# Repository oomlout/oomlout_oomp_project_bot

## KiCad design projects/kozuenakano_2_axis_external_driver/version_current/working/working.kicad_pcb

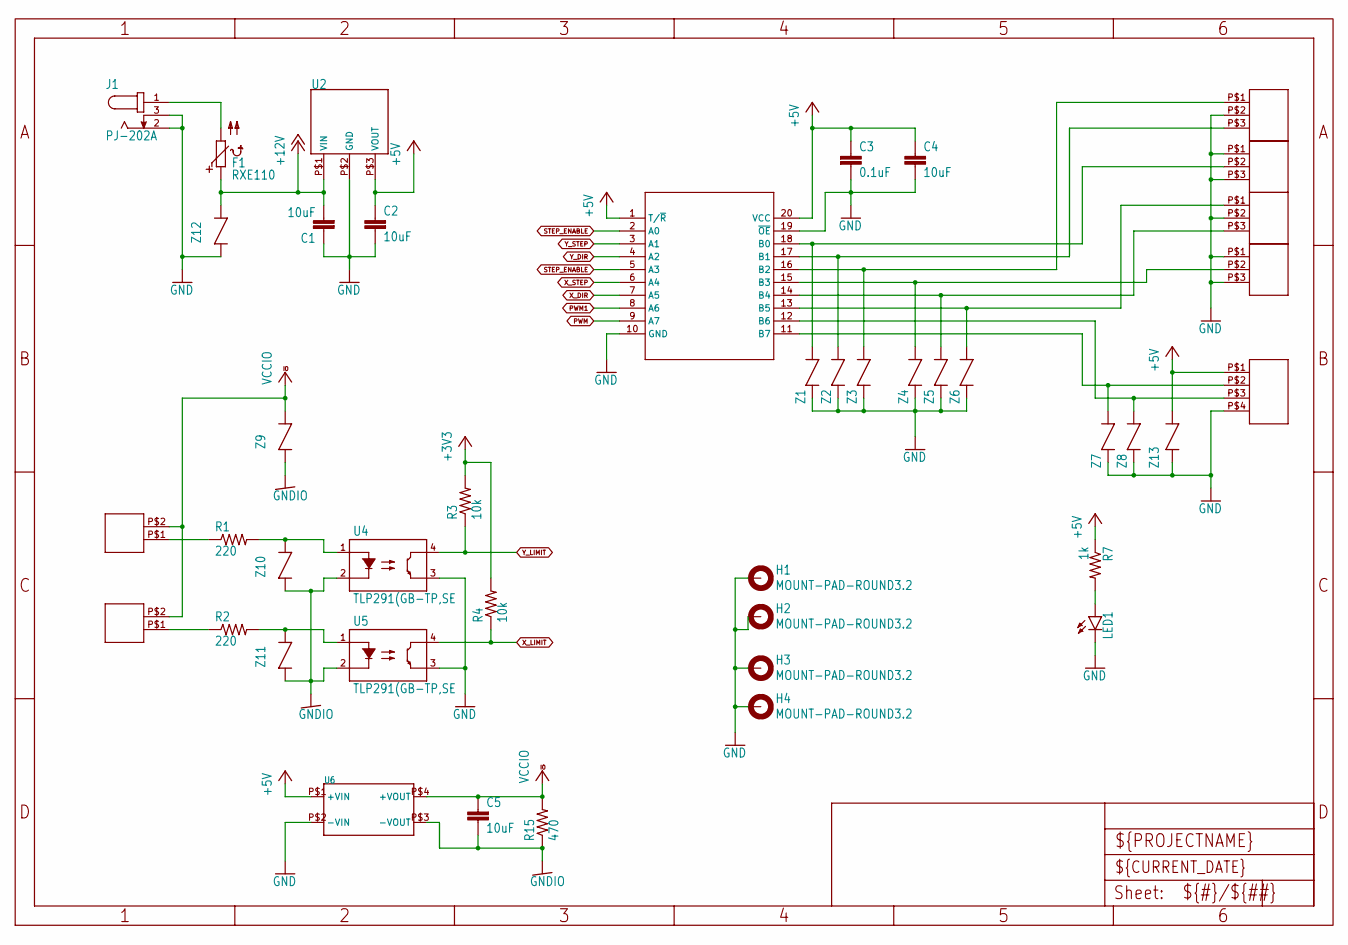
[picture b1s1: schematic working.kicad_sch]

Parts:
C1, C2, C4, C5: 10uF; C0805
C3: 0.1uF; C0603
CN1, CN2, CN3, CN4: ETB43034G000Z
CN7: ETB43044G000Z
CN8, CN9: ETB43024G000Z
F1: RXE110
H1, H2, H3, H4: MOUNT-PAD-ROUND3.2; 3,2-PAD
J1: PJ-202A; CUI_PJ-202A
LED1: LED3MM
R1, R2: 220; R0603
R3, R4: 10k; R0603
R7: 1k; R0603
R15: 470; R0603
U2: BP5293-50BP5293_SIDE; BP5293_SIDE
U3: MC74ACT245DWR2G; SOIC-20WB_ONS
U4, U5: TLP291(GB-TP,SE; SOIC127P700X220-4N
U6: MAU102; MAU100_SINGLE
Z1, Z2, Z3, Z4, Z5, Z6, Z7, Z8, Z9, Z10, Z11, Z13: MLVC06V012C210; 0603
Z12: MLVC06V026C120; 0603

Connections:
+3V3: R3.2, R4.2; also elsewhere on the board
+5V: C2.2, C3.1, C4.2, CN7.P$1 (1), R7.1, U2.P$3 (VOUT), U3.1 (T/~R), U3.20 (VCC), U6.P$1 (+VIN), Z13.1; also elsewhere on the board
+12V: C1.2, F1.P$1 (1), U2.P$1 (VIN), Z12.1
GND: C1.1, C2.1, C3.2, C4.1, CN1.P$1 (1), CN1.P$3 (3), CN2.P$2 (2), CN3.P$1 (1), CN3.P$3 (3), CN4.P$2 (2), CN7.P$4 (4), H1.B3,2, H2.B3,2, H3.B3,2, H4.B3,2, J1.2, J1.3, LED1.K (C), U2.P$2 (GND), U3.10 (GND), U3.19 (~OE), U4.3 (EMIT), U5.3 (EMIT), U6.P$2 (-VIN), Z1.2, Z2.2, Z3.2, Z4.2, Z5.2, Z6.2, Z7.2, Z8.2, Z12.2, Z13.2; also elsewhere on the board
GNDIO: C5.1, R15.1, U4.2 (C), U5.2 (C), U6.P$3 (-VOUT), Z9.2, Z10.2, Z11.2
LED1_PWM_5: CN7.P$3 (3), U3.12 (B6), Z8.1
LED_PWM_5: CN7.P$2 (2), U3.11 (B7), Z7.1
unnamed: F1.P$2 (2), J1.1
unnamed: LED1.A, R7.2
unnamed: R1.2, U4.1 (A), Z10.1
unnamed: R2.2, U5.1 (A), Z11.1
PWM: U3.9 (A7); also elsewhere on the board
PWM1: U3.8 (A6); also elsewhere on the board
STEP_ENABLE: U3.2 (A0), U3.5 (A3); also elsewhere on the board
STEP_EN_X_5: CN3.P$2 (2), U3.15 (B3), Z4.1
STEP_EN_Y_5: CN1.P$2 (2), U3.18 (B0), Z1.1
VCCIO: C5.2, CN8.P$2 (2), CN9.P$2 (2), R15.2, U6.P$4 (+VOUT), Z9.1
X_DIR: U3.7 (A5); also elsewhere on the board
X_DIR_5: CN4.P$1 (1), U3.13 (B5), Z6.1
X_LIMIT: R4.1, U5.4 (COL); also elsewhere on the board
X_LIMIT_IO: CN9.P$1 (1), R2.1
X_STEP: U3.6 (A4); also elsewhere on the board
X_STEP_5: CN4.P$3 (3), U3.14 (B4), Z5.1
Y_DIR: U3.4 (A2); also elsewhere on the board
Y_DIR_5: CN2.P$1 (1), U3.16 (B2), Z3.1
Y_LIMIT: R3.1, U4.4 (COL); also elsewhere on the board
Y_LIMIT_IO: CN8.P$1 (1), R1.1
Y_STEP: U3.3 (A1); also elsewhere on the board
Y_STEP_5: CN2.P$3 (3), U3.17 (B1), Z2.1

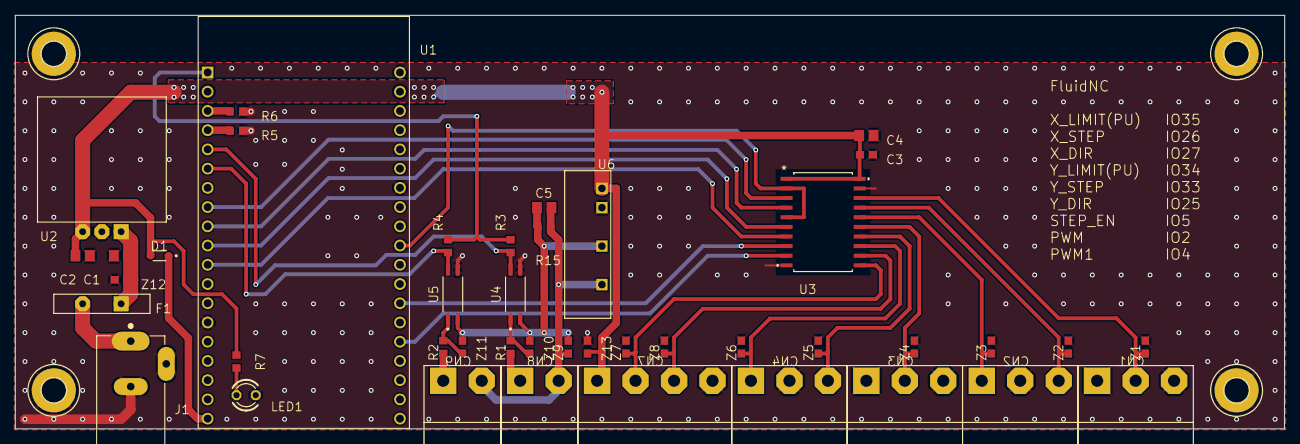
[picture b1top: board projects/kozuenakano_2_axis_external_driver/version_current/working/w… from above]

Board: 2 copper layers, 167.6 x 54.6 mm, 47 parts (0 on the bottom side), 32 nets.

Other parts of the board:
D1: BAT760-7; SOD2513X120N
R5, R6: 100k; R0603
U1: ESP32-DEVKITC-32D; MODULE_ESP32-DEVKITC-32D

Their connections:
+3V3: U1.1; also elsewhere on the board
+5V: D1.A; also elsewhere on the board
GND: R5.1, R6.1, U1.14, U1.20, U1.26; also elsewhere on the board
unnamed: D1.C, U1.19
unnamed: R6.2, U1.3
unnamed: R5.2, U1.4
PWM: U1.34; also elsewhere on the board
PWM1: U1.32; also elsewhere on the board
STEP_ENABLE: U1.29; also elsewhere on the board
X_DIR: U1.11; also elsewhere on the board
X_LIMIT: U1.6; also elsewhere on the board
X_STEP: U1.10; also elsewhere on the board
Y_DIR: U1.9; also elsewhere on the board
Y_LIMIT: U1.5; also elsewhere on the board
Y_STEP: U1.8; also elsewhere on the board

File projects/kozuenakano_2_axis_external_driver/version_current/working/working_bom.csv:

"Id";"Designator";"Footprint";"Quantity";"Designation";"Supplier and ref";
1;"C5,C2,C1,C4";"C0805";4;"10uF";;;
2;"Z13,Z9,Z7,Z3,Z1,Z11,Z4,Z6,Z5,Z8,Z10,Z2";"0603";12;"MLVC06V012C210";;;
3;"CN1,CN4,CN3,CN2";"ETB43034G000Z";4;"ETB43034G000Z";;;
4;"LED1";"LED3MM";1;"";;;
5;"R6,R5";"R0603";2;"100k";;;
6;"U5,U4";"SOIC127P700X220-4N";2;"TLP291(GB-TP,SE";;;
7;"C3";"C0603";1;"0.1uF";;;
8;"R7";"R0603";1;"1k";;;
9;"H2,H4,H3,H1";"3,2-PAD";4;"MOUNT-PAD-ROUND3.2";;;
10;"R3,R4";"R0603";2;"10k";;;
11;"Z12";"0603";1;"MLVC06V026C120";;;
12;"J1";"CUI_PJ-202A";1;"PJ-202A";;;
13;"CN8,CN9";"ETB43024G000Z";2;"ETB43024G000Z";;;
14;"U3";"SOIC-20WB_ONS";1;"MC74ACT245DWR2G";;;
15;"D1";"SOD2513X120N";1;"BAT760-7";;;
16;"CN7";"ETB43044G000Z";1;"ETB43044G000Z";;;
17;"U6";"MAU100_SINGLE";1;"MAU102";;;
18;"F1";"RXE110";1;"RXE110";;;
19;"U1";"MODULE_ESP32-DEVKITC-32D";1;"ESP32-DEVKITC-32D";;;
20;"R1,R2";"R0603";2;"220";;;
21;"R15";"R0603";1;"470";;;
22;"U2";"BP5293_SIDE";1;"BP5293-50BP5293_SIDE";;;

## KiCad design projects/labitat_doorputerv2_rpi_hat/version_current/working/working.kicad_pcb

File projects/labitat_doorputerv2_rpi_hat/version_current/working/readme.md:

# doorputerv2_rpi_hat by labitat  
This is a harvested standardized copy of a project from github.  
The original project can be found at:  
https://github.com/labitat/doorputerv2_rpi_hat  
Please consult that link for additional, details, files, and license information.  
Note: It was auto harvested and if the original repo had more than one board file or anything out of the ordinary the files here are likely not representative.

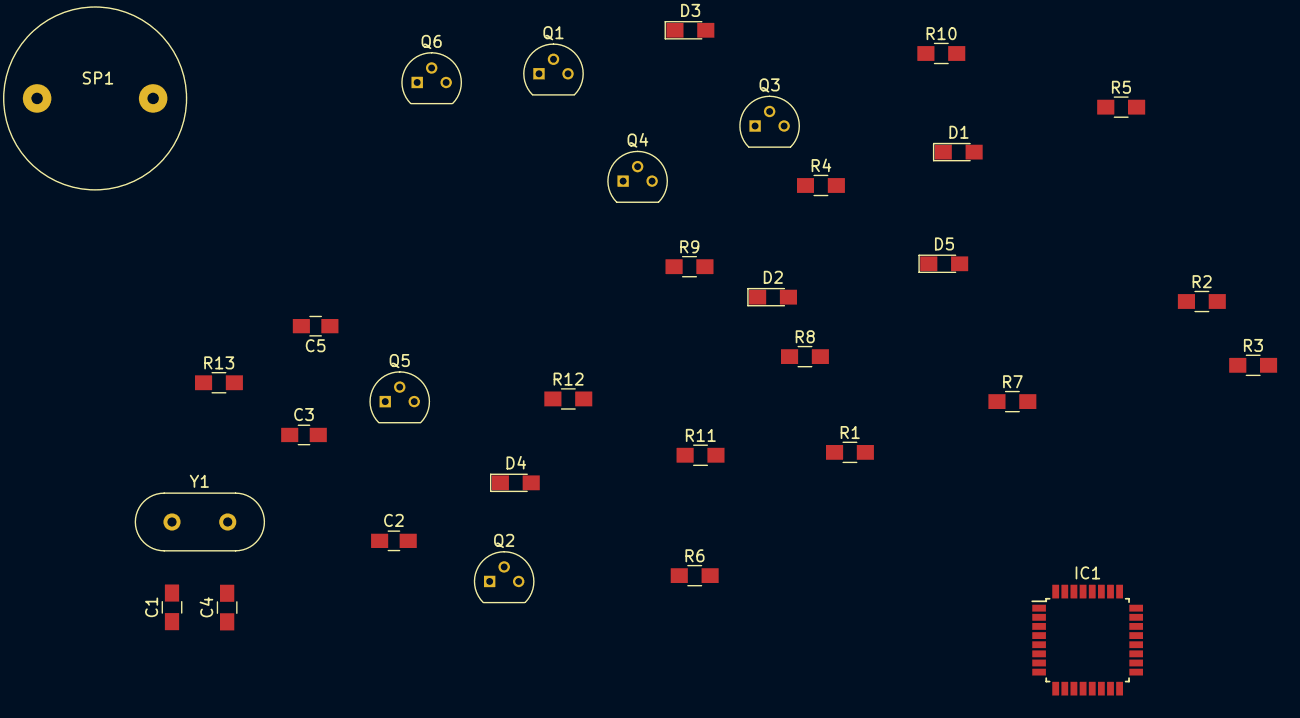
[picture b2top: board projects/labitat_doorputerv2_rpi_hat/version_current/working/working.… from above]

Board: 2 copper layers, 32 parts (0 on the bottom side), 23 nets, no tracks yet.

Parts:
C1, C4: 22pF; C_0805_HandSoldering
C2, C3, C5: 100nF; C_0805_HandSoldering
D1, D2, D3, D4, D5: LED; LED_0805_HandSoldering
IC1: ATMEGA328P; LQFP-32_7x7mm_Pitch0.8mm
Q1, Q2, Q3, Q4, Q5, Q6: BC547; TO-92_Molded_Narrow
R1, R2, R3, R4, R5, R6, R7, R8, R9, R10, R11, R12: R_Small; R_0805_HandSoldering
R13: 10K; R_0805_HandSoldering
SP1: BUZZER
Y1: 16MHz; Crystal_HC49-U_Vertical

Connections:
+5V: C2.2, C3.2, IC1.4, IC1.6, IC1.18, IC1.20, R1.1, R2.1, R3.1, R4.1, R5.1, R11.1, R13.1
/Arduino/avr_reset: C5.2, IC1.29, R13.2
GND: C1.1, C2.1, C3.1, C4.1, C5.1, IC1.3, IC1.5, IC1.21, Q1.3, Q2.3, Q3.3, Q4.3, Q5.3, Q6.3
unnamed: C1.2, IC1.7, Y1.1
unnamed: C4.2, IC1.8, Y1.2
unnamed: D1.1, Q1.1
unnamed: D1.2, R1.2
unnamed: D2.1, Q2.1
unnamed: D2.2, R2.2
unnamed: D3.1, Q3.1
unnamed: D3.2, R3.2
unnamed: D4.1, Q4.1
unnamed: D4.2, R4.2
unnamed: D5.1, Q5.1
unnamed: D5.2, R5.2
unnamed: Q1.2, R6.2
unnamed: Q2.2, R7.2
unnamed: Q3.2, R8.2
unnamed: Q4.2, R9.2
unnamed: Q5.2, R10.2
unnamed: Q6.1, SP1.2
unnamed: Q6.2, R12.2
unnamed: R11.2, SP1.1

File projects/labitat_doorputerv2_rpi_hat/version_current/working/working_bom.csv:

"Id";"Designator";"Footprint";"Quantity";"Designation";"Supplier and ref";
1;"C1,C4";"C_0805_HandSoldering";2;"22pF";;;
2;"C2,C3,C5";"C_0805_HandSoldering";3;"100nF";;;
3;"D1,D2,D3,D4,D5";"LED_0805_HandSoldering";5;"LED";;;
4;"IC1";"LQFP-32_7x7mm_Pitch0.8mm";1;"ATMEGA328P";;;
5;"Q1,Q2,Q3,Q4,Q5,Q6";"TO-92_Molded_Narrow";6;"BC547";;;
6;"R1,R2,R3,R4,R5,R6,R7,R8,R9,R10,R11,R12";"R_0805_HandSoldering";12;"R_Small";;;
7;"R13";"R_0805_HandSoldering";1;"10K";;;
8;"SP1";"BUZZER";1;"BUZZER";;;
9;"Y1";"Crystal_HC49-U_Vertical";1;"16MHz";;;

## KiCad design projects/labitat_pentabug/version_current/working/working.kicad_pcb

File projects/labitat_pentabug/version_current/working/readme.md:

# pentabug by labitat  
This is a harvested standardized copy of a project from github.  
The original project can be found at:  
https://github.com/labitat/pentabug  
Please consult that link for additional, details, files, and license information.  
Note: It was auto harvested and if the original repo had more than one board file or anything out of the ordinary the files here are likely not representative.

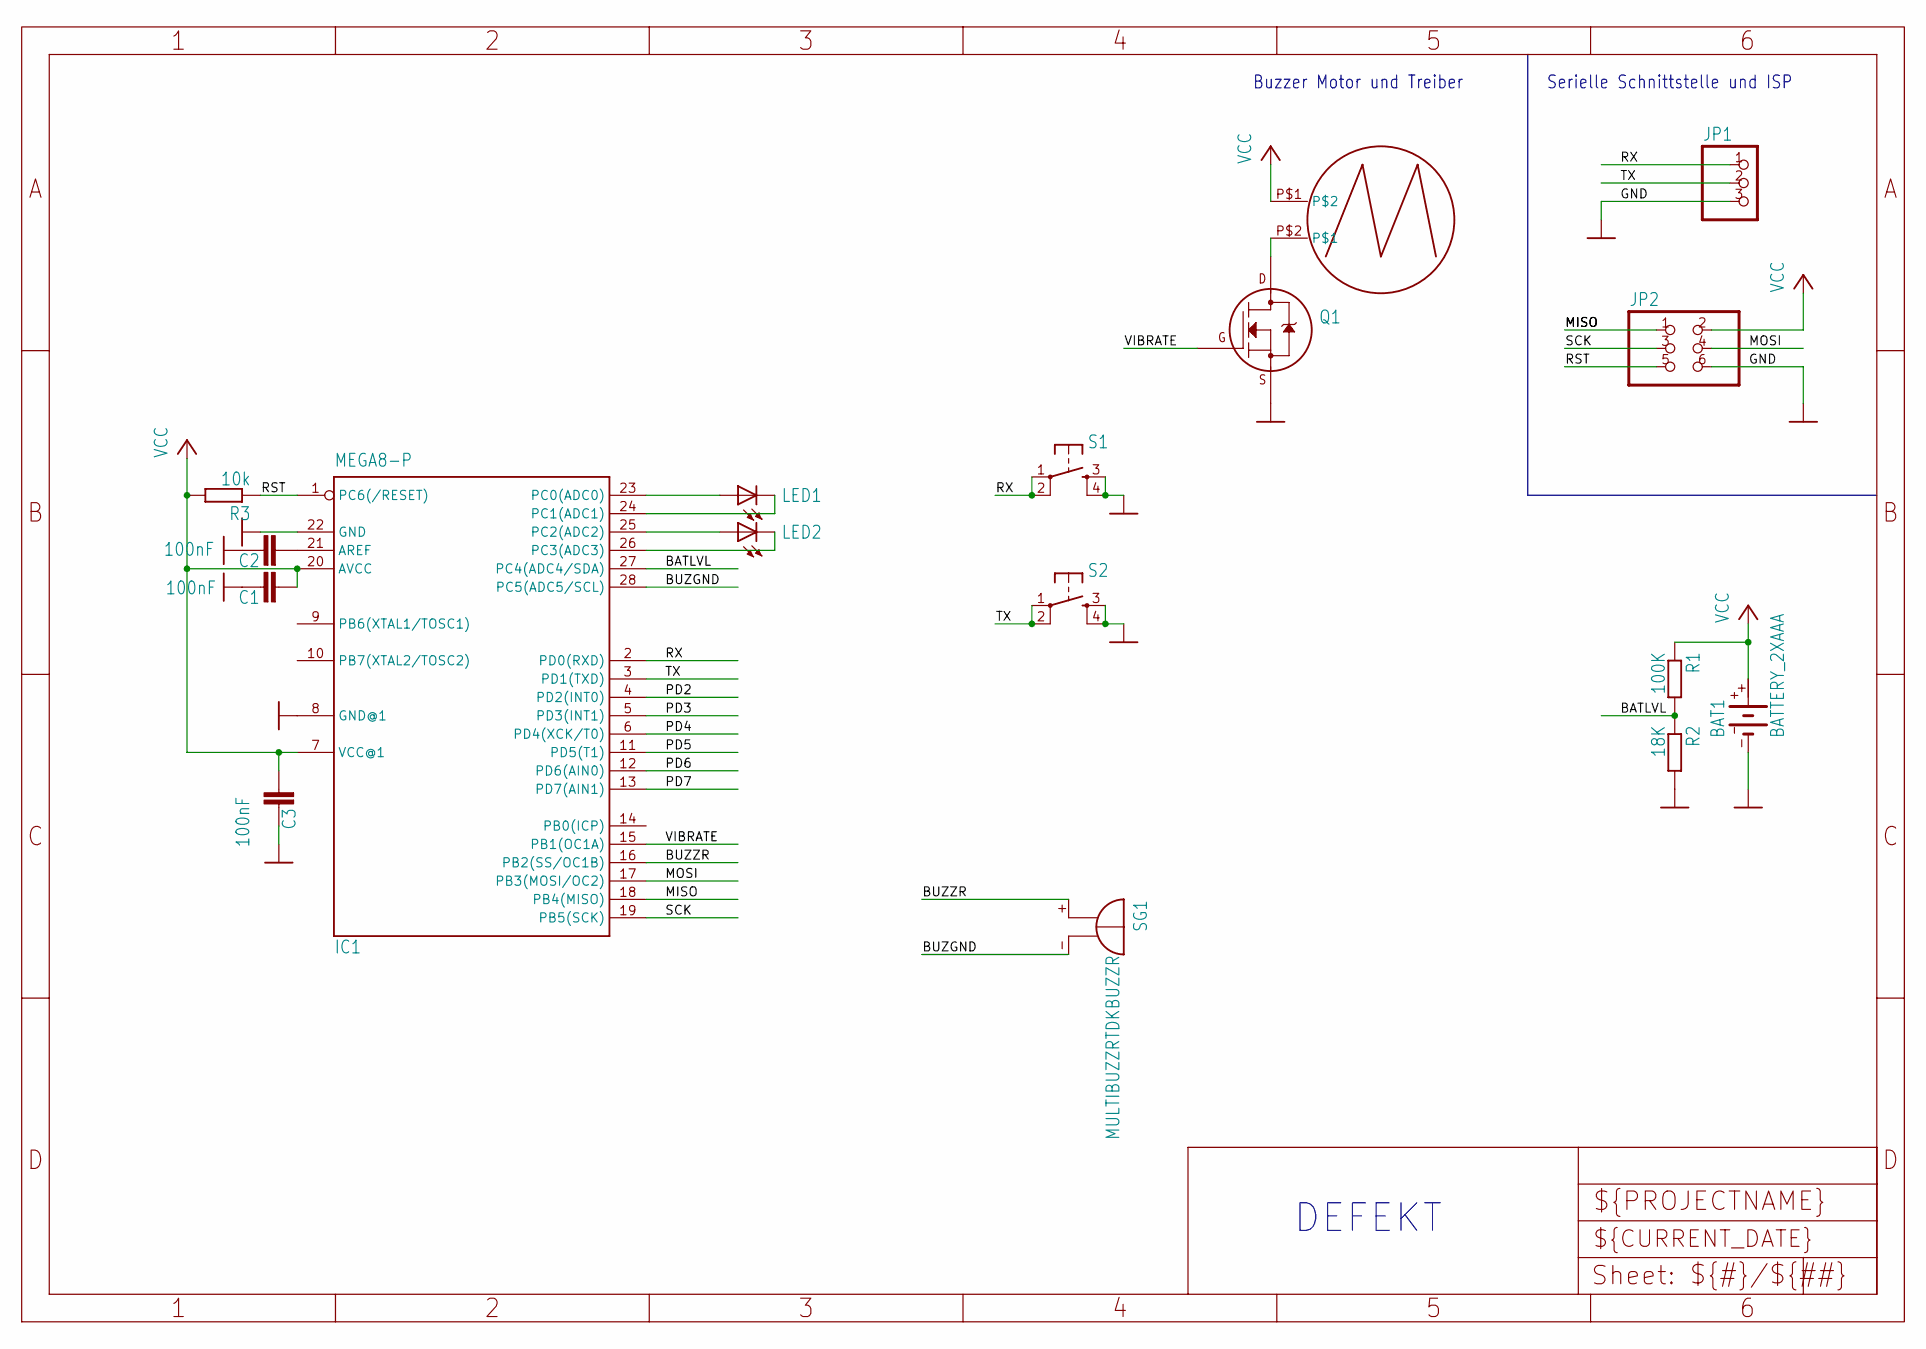
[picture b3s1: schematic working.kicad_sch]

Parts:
BAT1: BATTERY_2XAAA
C1, C2, C3: 100nF; C025-024X044
IC1: MEGA8-P; DIL28-3
JP1: PINHD-1X3; 1X03
JP2: PINHD-2X3; 2X03
LED1, LED2: LED5MM
Q1: 2N700_TO92; TO-92
R1: 100K; 0207_10
R2: 18K; 0207_10
R3: 10k; 0207_10
S1, S2: TAC_SWITCHPTH; TACTILE-PTH
SG1: MULTIBUZZRTDKBUZZR; BUZZRTDK
U$1: VIBRAMOTOR; LA4-432

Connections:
BATLVL: IC1.27 (PC4(ADC4/SDA)), R1.2, R2.1
BATTLVL: IC1.26 (PC3(ADC3)), LED2.K (C)
BUZGND: IC1.28 (PC5(ADC5/SCL)), SG1.-
BUZZR: IC1.16 (PB2(SS/OC1B)), SG1.+
GND: BAT1.-, C1.1, C2.1, C3.1, IC1.8 (GND@1), IC1.22 (GND), JP1.3, JP2.6, Q1.1 (S), R2.2, S1.3, S1.4, S2.3, S2.4
MISO: IC1.18 (PB4(MISO)), JP2.1
MOSI: IC1.17 (PB3(MOSI/OC2)), JP2.4
unnamed: IC1.23 (PC0(ADC0)), LED1.A
unnamed: IC1.25 (PC2(ADC2)), LED2.A
unnamed: Q1.3 (D), U$1.P$2
unnamed: IC1.24 (PC1(ADC1)), LED1.K (C)
unnamed: C2.2, IC1.21 (AREF)
PD2: IC1.4 (PD2(INT0))
PD3: IC1.5 (PD3(INT1))
PD4: IC1.6 (PD4(XCK/T0))
PD5: IC1.11 (PD5(T1))
PD6: IC1.12 (PD6(AIN0))
PD7: IC1.13 (PD7(AIN1))
RST: IC1.1 (PC6(/RESET)), JP2.5, R3.1
RX: IC1.2 (PD0(RXD)), JP1.1, S1.1, S1.2
SCK: IC1.19 (PB5(SCK)), JP2.3
TX: IC1.3 (PD1(TXD)), JP1.2, S2.1, S2.2
VCC: BAT1.+, C1.2, C3.2, IC1.7 (VCC@1), IC1.20 (AVCC), JP2.2, R1.1, R3.2, U$1.P$1
VIBRATE: IC1.15 (PB1(OC1A)), Q1.2 (G)

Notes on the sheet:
Buzzer Motor und Treiber
DEFEKT~{}
Serielle Schnittstelle und ISP

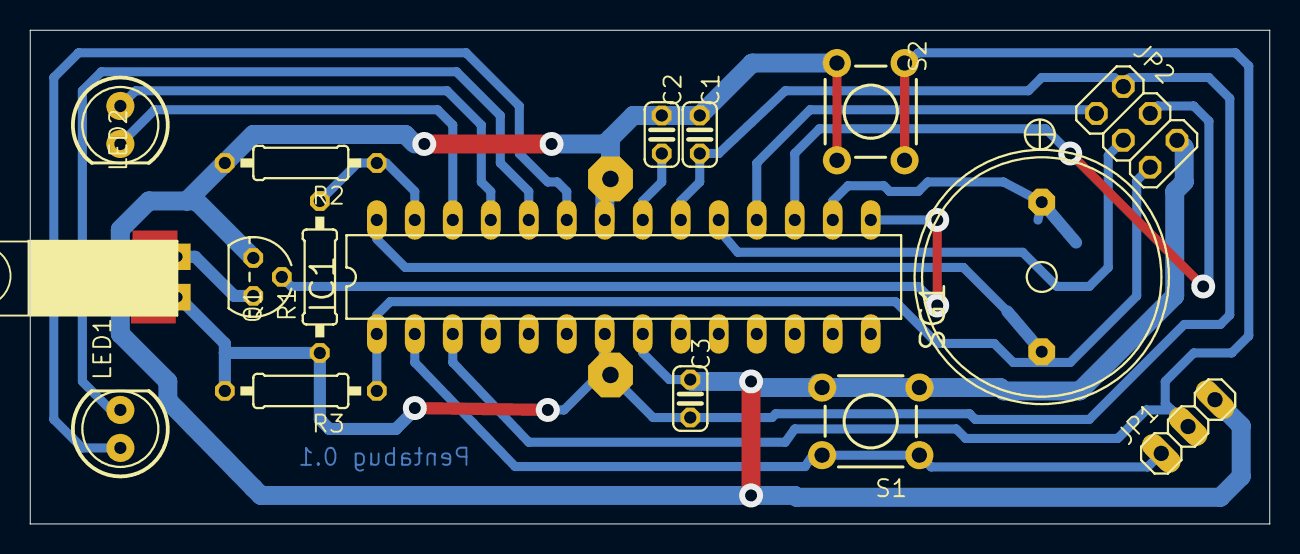
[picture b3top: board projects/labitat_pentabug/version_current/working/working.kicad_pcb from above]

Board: 2 copper layers, 82.9 x 33.0 mm, 17 parts (1 on the bottom side), 18 nets.

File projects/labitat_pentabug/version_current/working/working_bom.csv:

"Id";"Designator";"Footprint";"Quantity";"Designation";"Supplier and ref";
1;"JP1";"1X03";1;"";;;
2;"C3,C2,C1";"C025-024X044";3;"100nF";;;
3;"R2";"0207_10";1;"18K";;;
4;"IC1";"DIL28-3";1;"ATMEGA88";;;
5;"R3";"0207_10";1;"10k";;;
6;"SG1";"BUZZRTDK";1;"MULTIBUZZRTDKBUZZR";;;
7;"U$1";"LA4-432";1;"VIBRAMOTOR";;;
8;"S1,S2";"TACTILE-PTH";2;"";;;
9;"R1";"0207_10";1;"100K";;;
10;"LED2,LED1";"LED5MM";2;"";;;
11;"Q1";"TO-92";1;"";;;
12;"JP2";"2X03";1;"";;;
13;"BAT1";"BATTERY_2XAAA";1;"BATTERY_2XAAA";;;

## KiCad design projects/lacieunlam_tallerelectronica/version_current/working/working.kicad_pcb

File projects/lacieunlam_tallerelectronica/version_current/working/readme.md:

# TallerElectronica by LacieUnlam  
This is a harvested standardized copy of a project from github.  
The original project can be found at:  
https://github.com/LacieUnlam/TallerElectronica  
Please consult that link for additional, details, files, and license information.  
Note: It was auto harvested and if the original repo had more than one board file or anything out of the ordinary the files here are likely not representative.

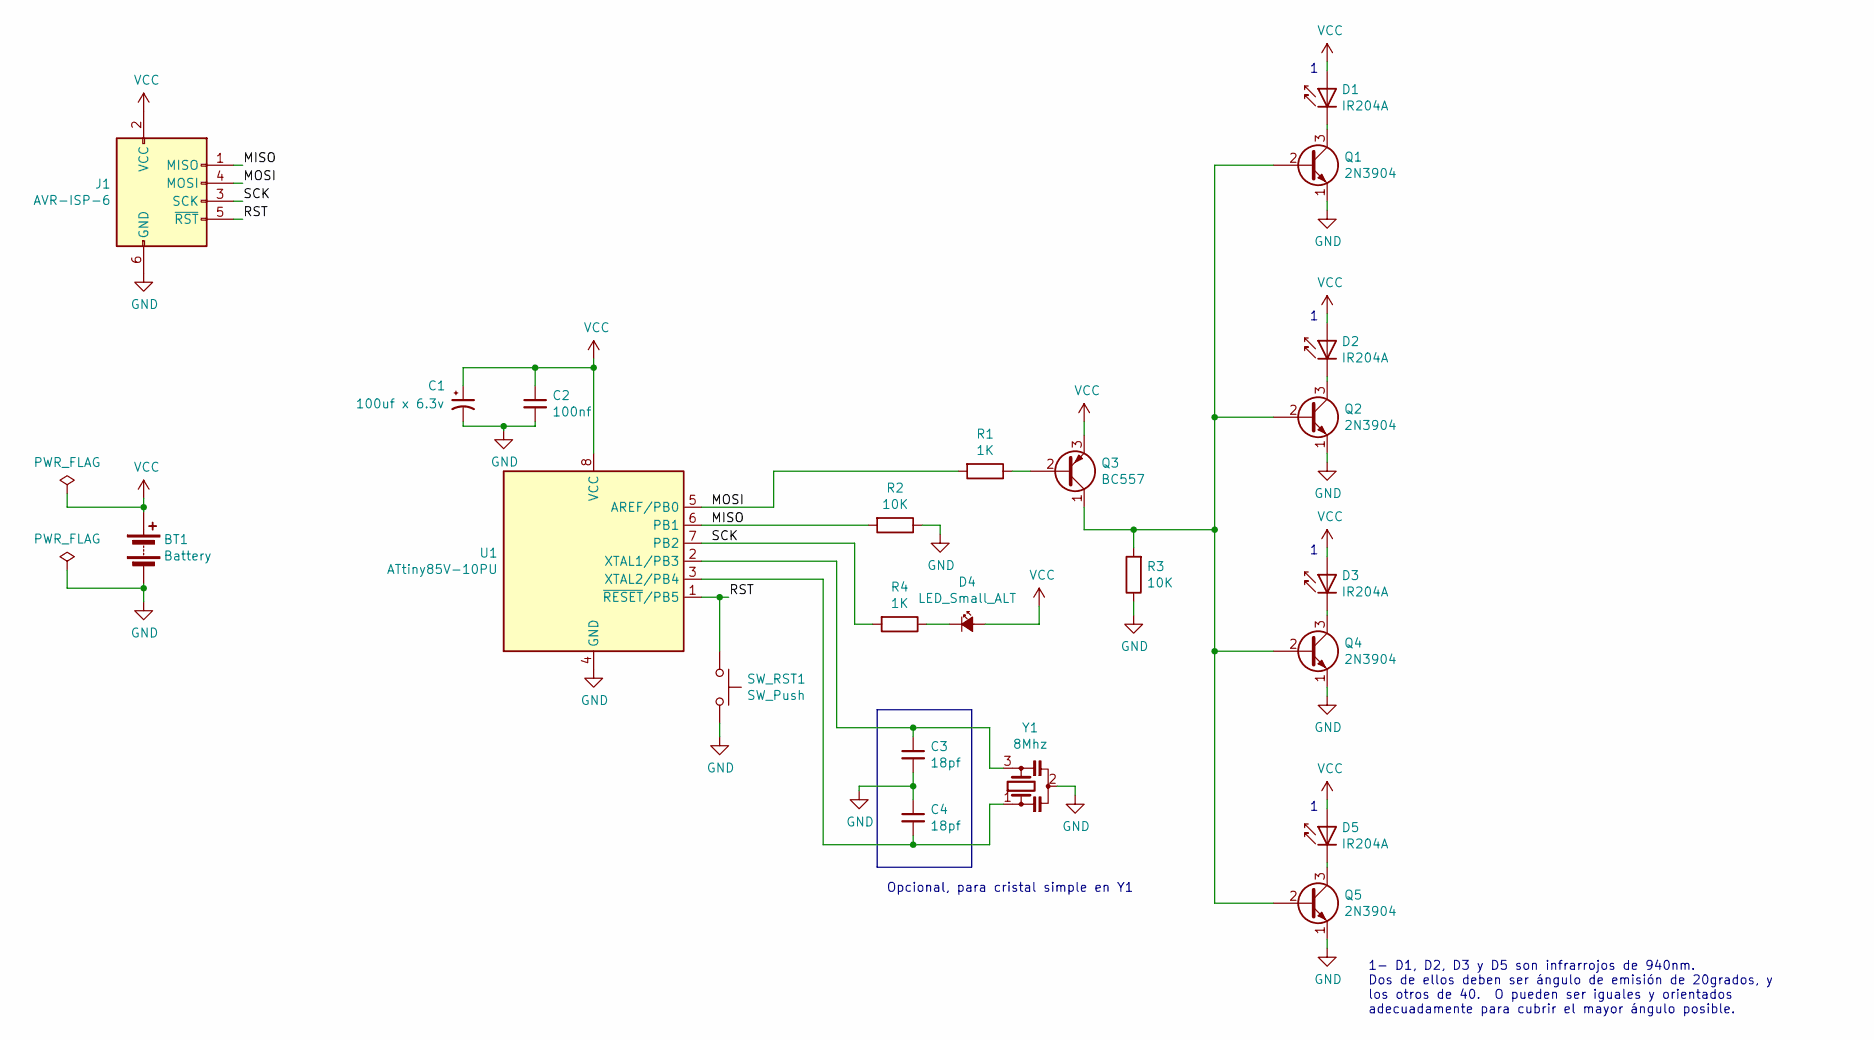
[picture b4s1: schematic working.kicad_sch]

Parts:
BT1: Battery; PinHeader_1x02_P2.54mm_Vertical
C1: 100uf x 6.3v; CP_Radial_D6.3mm_P2.50mm
C2: 100nf; C_Disc_D7.5mm_W2.5mm_P5.00mm
C3, C4: 18pf; C_Disc_D3.0mm_W2.0mm_P2.50mm
D1, D2, D3, D5: IR204A; LED_D3.0mm_IRBlack
D4: LED_Small_ALT; LED_D3.0mm
J1: AVR-ISP-6; PinHeader_2x03_P2.54mm_Vertical
Q1, Q2, Q4, Q5: 2N3904; TO-92_Inline
Q3: BC557; TO-92_Inline
R1, R4: 1K; R_Axial_DIN0309_L9.0mm_D3.2mm_P12.70mm_Horizontal
R2, R3: 10K; R_Axial_DIN0309_L9.0mm_D3.2mm_P12.70mm_Horizontal
SW_RST1: SW_Push; SW_PUSH_6mm_H5mm
U1: ATtiny85V-10PU; DIP-8_W7.62mm
Y1: 8Mhz; Resonator-3Pin_W10.0mm_H5.0mm

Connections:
/MISO: J1.1 (MISO), R2.2, U1.6 (PB1)
/MOSI: J1.4 (MOSI), R1.2, U1.5 (AREF/PB0)
/RST: J1.5 (~RST), SW_RST1.1, U1.1 (~RESET/PB5)
/SCK: J1.3 (SCK), R4.2, U1.7 (PB2)
GND: BT1.2 (-), C1.2, C2.2, C3.2, C4.1, J1.6 (GND), Q1.1 (E), Q2.1 (E), Q4.1 (E), Q5.1 (E), R2.1, R3.1, SW_RST1.2, U1.4 (GND), Y1.2
unnamed: C3.1, U1.2 (XTAL1/PB3), Y1.3
unnamed: C4.2, U1.3 (XTAL2/PB4), Y1.1
unnamed: D1.1 (K), Q1.3 (C)
unnamed: D2.1 (K), Q2.3 (C)
unnamed: D3.1 (K), Q4.3 (C)
unnamed: D4.1 (K), R4.1
unnamed: D5.1 (K), Q5.3 (C)
unnamed: Q1.2 (B), Q2.2 (B), Q3.1 (C), Q4.2 (B), Q5.2 (B), R3.2
unnamed: Q3.2 (B), R1.1
VCC: BT1.1 (+), C1.1, C2.1, D1.2 (A), D2.2 (A), D3.2 (A), D4.2 (A), D5.2 (A), J1.2 (VCC), Q3.3 (E), U1.8 (VCC)

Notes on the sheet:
Opcional, para cristal simple en Y1
1- D1, D2, D3 y D5 son infrarrojos de 940nm. Dos de ellos deben ser ángulo de emisión de 20grados, y los otros de 40. O pueden ser iguales y orientados adecuadamente para cubrir el mayor ángulo posible.

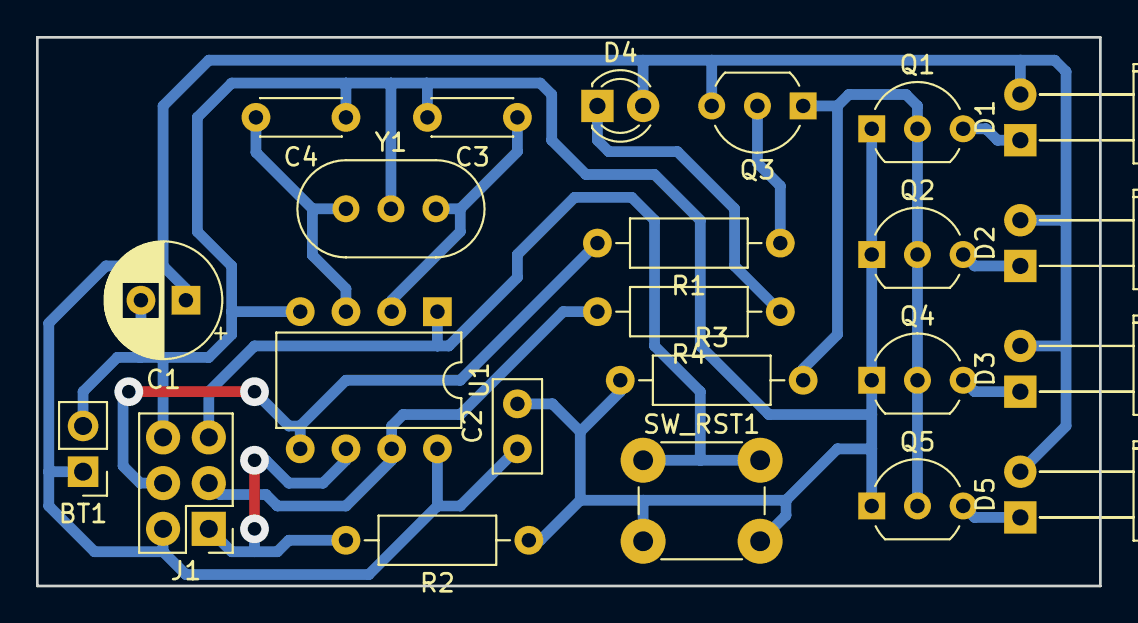
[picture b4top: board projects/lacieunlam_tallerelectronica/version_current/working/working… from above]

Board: 2 copper layers, 59.1 x 30.5 mm, 23 parts (0 on the bottom side), 15 nets.

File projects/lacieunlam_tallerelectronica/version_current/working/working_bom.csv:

"Id";"Designator";"Footprint";"Quantity";"Designation";"Supplier and ref";
1;"R1,R4";"R_Axial_DIN0207_L6.3mm_D2.5mm_P10.16mm_Horizontal";2;"1K";;;
2;"R2,R3";"R_Axial_DIN0207_L6.3mm_D2.5mm_P10.16mm_Horizontal";2;"10K";;;
3;"SW_RST1";"SW_PUSH_6mm_H5mm";1;"SW_Push";;;
4;"J1";"PinHeader_2x03_P2.54mm_Vertical";1;"AVR-ISP-6";;;
5;"C1";"CP_Radial_D6.3mm_P2.50mm";1;"100uf x 6.3v";;;
6;"C4,C3";"C_Disc_D4.3mm_W1.9mm_P5.00mm";2;"18pf";;;
7;"C2";"C_Disc_D5.0mm_W2.5mm_P2.50mm";1;"100nf";;;
8;"Q3";"TO-92_Inline_Wide";1;"BC557";;;
9;"Q1,Q2,Q4,Q5";"TO-92_Inline_Wide";4;"2N3904";;;
10;"D2,D3,D5,D1";"LED_D5.0mm_Horizontal_O6.35mm_Z3.0mm";4;"IR204A";;;
11;"BT1";"PinHeader_1x02_P2.54mm_Vertical";1;"Battery";;;
12;"D4";"LED_D3.0mm";1;"LED_Small_ALT";;;
13;"U1";"DIP-8_W7.62mm";1;"ATtiny85V-10PU";;;
14;"Y1";"Resonator-3Pin_W10.0mm_H5.0mm";1;"8Mhz";;;

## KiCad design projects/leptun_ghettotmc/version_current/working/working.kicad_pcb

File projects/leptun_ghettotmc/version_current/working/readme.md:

# OOMP Project  
## GhettoTMC  by leptun  
  
oomp key: oomp_projects_flat_leptun_ghettotmc  
(snippet of original readme)  
  
GhettoTMC  
  
  full source readme at [readme_src.md](readme_src.md)  
  
source repo at: [https://github.com/leptun/GhettoTMC](https://github.com/leptun/GhettoTMC)  
## Board  

## Schematic  

[schematic pdf](working_schematic.pdf)  
## Images

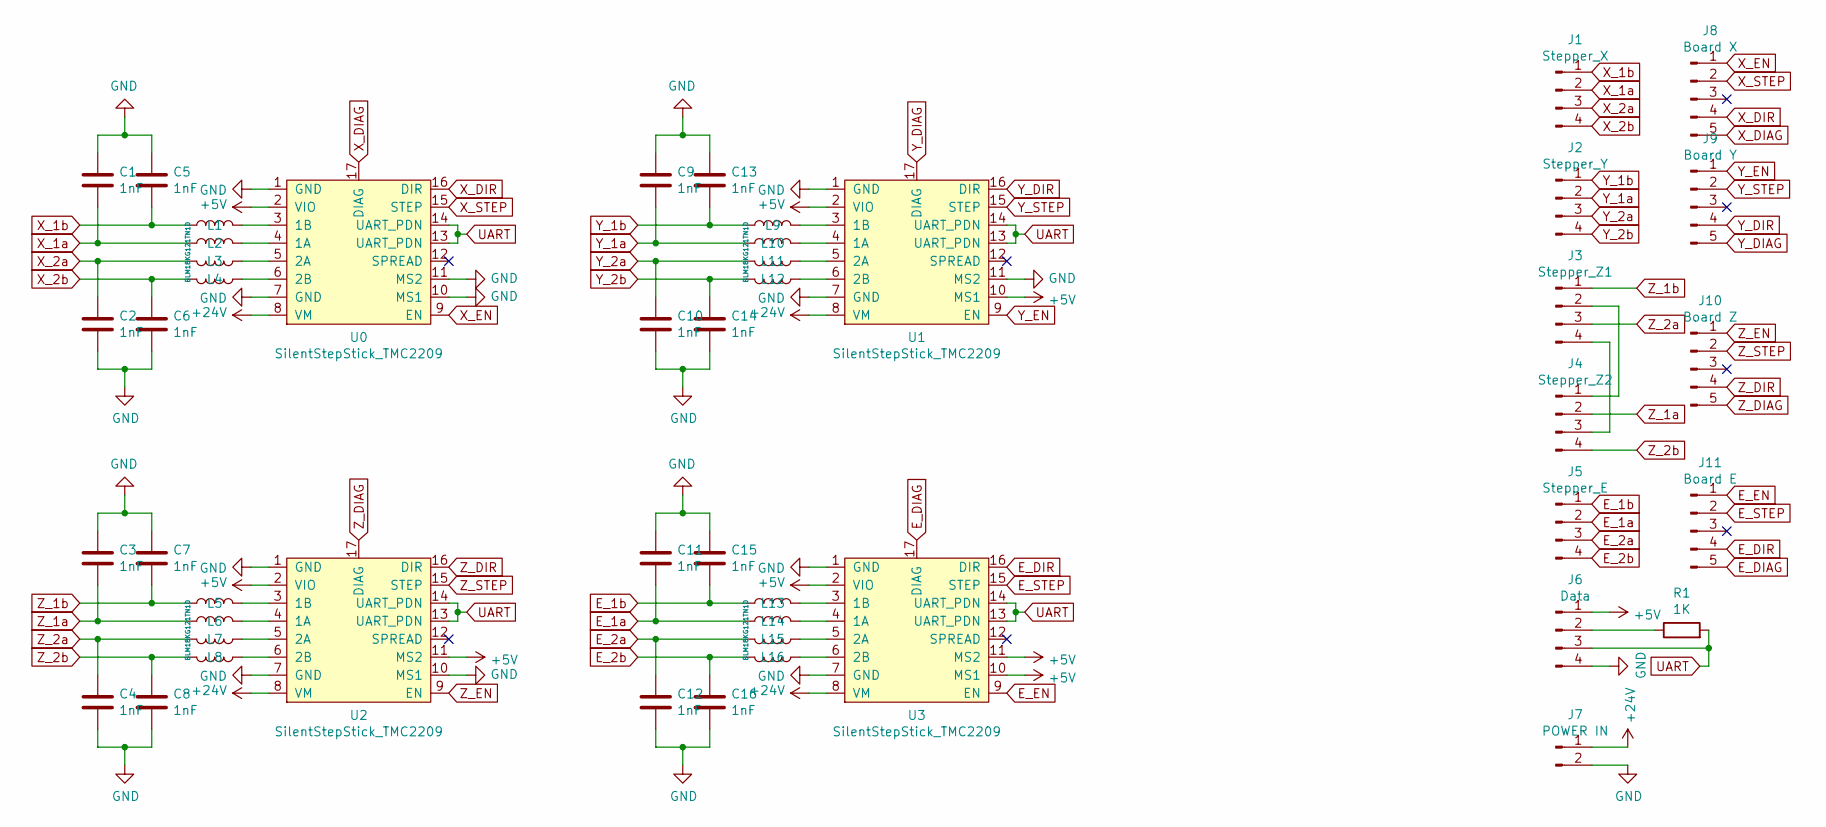
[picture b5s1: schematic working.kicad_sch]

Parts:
C1, C2, C3, C4, C5, C6, C7, C8, C9, C10, C11, C12, C13, C14, C15, C16: 1nF; C_Disc_D6.0mm_W2.5mm_P5.00mm
J1: Stepper_X; MOLEX_70553-0038
J2: Stepper_Y; MOLEX_70553-0038
J3: Stepper_Z1; MOLEX_70553-0038
J4: Stepper_Z2; MOLEX_70553-0038
J5: Stepper_E; MOLEX_70553-0038
J6: Data; MOLEX_70553-0038
J7: POWER IN; PhoenixContact_MC-G_02x5.08mm_Angled
J8: Board X; MOLEX_70553-0039
J9: Board Y; MOLEX_70553-0039
J10: Board Z; MOLEX_70553-0039
J11: Board E; MOLEX_70553-0039
L1, L2, L3, L4, L5, L6, L7, L8, L9, L10, L11, L12, L13, L14, L15, L16: BLM18KG121TN1D; L_0603_1608Metric_Pad1.05x0.95mm_HandSolder
R1: 1K; R_Axial_DIN0207_L6.3mm_D2.5mm_P10.16mm_Horizontal
U0, U1, U2, U3: SilentStepStick_TMC2209; SilentStepStick_TMC2209_Breakout

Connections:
+5V: J6.1, U0.2 (VIO), U1.2 (VIO), U1.10 (MS1), U2.2 (VIO), U2.11 (MS2), U3.2 (VIO), U3.10 (MS1), U3.11 (MS2)
+24V: J7.1, U0.8 (VM), U1.8 (VM), U2.8 (VM), U3.8 (VM)
E_1a: C11.2, J5.2, L14.1
E_1b: C15.2, J5.1, L13.1
E_2a: C12.1, J5.3, L15.2
E_2b: C16.1, J5.4, L16.2
E_DIAG: J11.5, U3.17 (DIAG)
E_DIR: J11.4, U3.16 (DIR)
E_EN: J11.1, U3.9 (EN)
E_STEP: J11.2, U3.15 (STEP)
GND: C1.1, C2.2, C3.1, C4.2, C5.1, C6.2, C7.1, C8.2, C9.1, C10.2, C11.1, C12.2, C13.1, C14.2, C15.1, C16.2, J6.4, J7.2, U0.1 (GND), U0.7 (GND), U0.10 (MS1), U0.11 (MS2), U1.1 (GND), U1.7 (GND), U1.11 (MS2), U2.1 (GND), U2.7 (GND), U2.10 (MS1), U3.1 (GND), U3.7 (GND)
unnamed: J3.2, J4.1
unnamed: J3.4, J4.3
unnamed: J6.2, R1.1
unnamed: L1.2, U0.3 (1B)
unnamed: L2.2, U0.4 (1A)
unnamed: L3.1, U0.5 (2A)
unnamed: L4.1, U0.6 (2B)
unnamed: L5.2, U2.3 (1B)
unnamed: L6.2, U2.4 (1A)
unnamed: L7.1, U2.5 (2A)
unnamed: L8.1, U2.6 (2B)
unnamed: L9.2, U1.3 (1B)
unnamed: L10.2, U1.4 (1A)
unnamed: L11.1, U1.5 (2A)
unnamed: L12.1, U1.6 (2B)
unnamed: L13.2, U3.3 (1B)
unnamed: L14.2, U3.4 (1A)
unnamed: L15.1, U3.5 (2A)
unnamed: L16.1, U3.6 (2B)
UART: J6.3, R1.2, U0.13 (UART_PDN), U0.14 (UART_PDN), U1.13 (UART_PDN), U1.14 (UART_PDN), U2.13 (UART_PDN), U2.14 (UART_PDN), U3.13 (UART_PDN), U3.14 (UART_PDN)
X_1a: C1.2, J1.2, L2.1
X_1b: C5.2, J1.1, L1.1
X_2a: C2.1, J1.3, L3.2
X_2b: C6.1, J1.4, L4.2
X_DIAG: J8.5, U0.17 (DIAG)
X_DIR: J8.4, U0.16 (DIR)
X_EN: J8.1, U0.9 (EN)
X_STEP: J8.2, U0.15 (STEP)
Y_1a: C9.2, J2.2, L10.1
Y_1b: C13.2, J2.1, L9.1
Y_2a: C10.1, J2.3, L11.2
Y_2b: C14.1, J2.4, L12.2
Y_DIAG: J9.5, U1.17 (DIAG)
Y_DIR: J9.4, U1.16 (DIR)
Y_EN: J9.1, U1.9 (EN)
Y_STEP: J9.2, U1.15 (STEP)
Z_1a: C3.2, J4.2, L6.1
Z_1b: C7.2, J3.1, L5.1
Z_2a: C4.1, J3.3, L7.2
Z_2b: C8.1, J4.4, L8.2
Z_DIAG: J10.5, U2.17 (DIAG)
Z_DIR: J10.4, U2.16 (DIR)
Z_EN: J10.1, U2.9 (EN)
Z_STEP: J10.2, U2.15 (STEP)

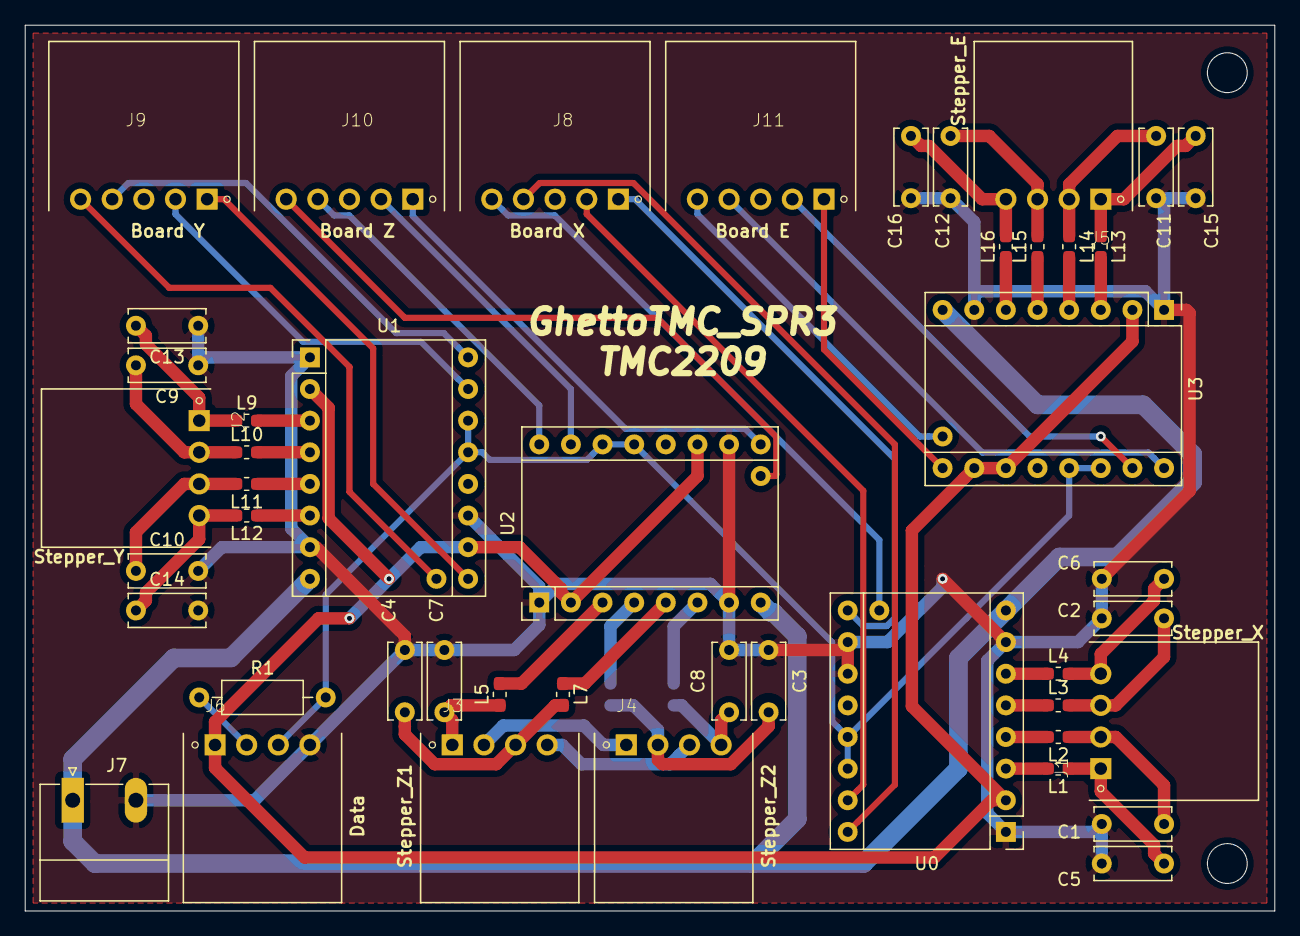
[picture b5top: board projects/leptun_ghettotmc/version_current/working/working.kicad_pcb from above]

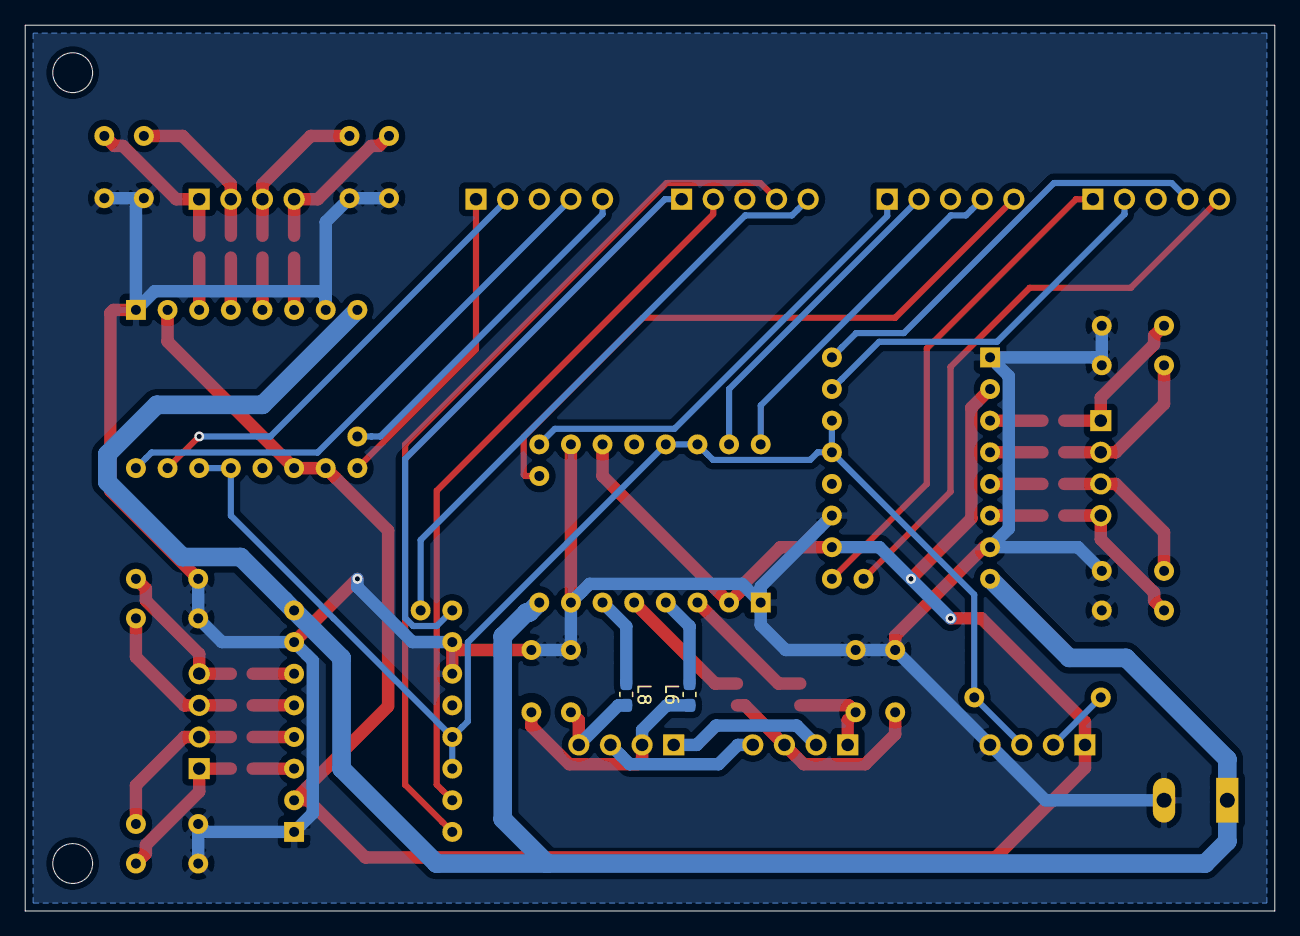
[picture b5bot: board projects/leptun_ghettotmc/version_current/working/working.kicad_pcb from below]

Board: 2 copper layers, 100.3 x 71.1 mm, 50 parts (2 on the bottom side), 55 nets.

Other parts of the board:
M1, M2: MountingHole_3.2mm_M3

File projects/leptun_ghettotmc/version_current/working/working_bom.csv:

"Id";"Designator";"Footprint";"Quantity";"Designation";"Supplier and ref";
1;"U3,U2,U1,U0";"SilentStepStick_TMC2209_Breakout";4;"SilentStepStick_TMC2209";;;
2;"R1";"R_Axial_DIN0207_L6.3mm_D2.5mm_P10.16mm_Horizontal";1;"1K";;;
3;"L16,L15,L14,L13,L12,L11,L10,L9,L8,L7,L6,L5,L4,L3,L2,L1";"L_0603_1608Metric_Pad1.05x0.95mm_HandSolder";16;"BLM18KG121TN1D";;;
4;"J11";"MOLEX_70553-0039";1;"Board E";;;
5;"J10";"MOLEX_70553-0039";1;"Board Z";;;
6;"J9";"MOLEX_70553-0039";1;"Board Y";;;
7;"J8";"MOLEX_70553-0039";1;"Board X";;;
8;"J7";"PhoenixContact_MC-G_02x5.08mm_Angled";1;"POWER IN";;;
9;"J6";"MOLEX_70553-0038";1;"Data";;;
10;"J5";"MOLEX_70553-0038";1;"Stepper_E";;;
11;"J4";"MOLEX_70553-0038";1;"Stepper_Z2";;;
12;"J3";"MOLEX_70553-0038";1;"Stepper_Z1";;;
13;"J2";"MOLEX_70553-0038";1;"Stepper_Y";;;
14;"J1";"MOLEX_70553-0038";1;"Stepper_X";;;
15;"C16,C15,C14,C13,C12,C11,C10,C9,C8,C7,C6,C5,C4,C3,C2,C1";"C_Disc_D6.0mm_W2.5mm_P5.00mm";16;"1nF";;;
